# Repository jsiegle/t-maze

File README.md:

t-maze
======

Arduino-based hardware and software for controlling a maze

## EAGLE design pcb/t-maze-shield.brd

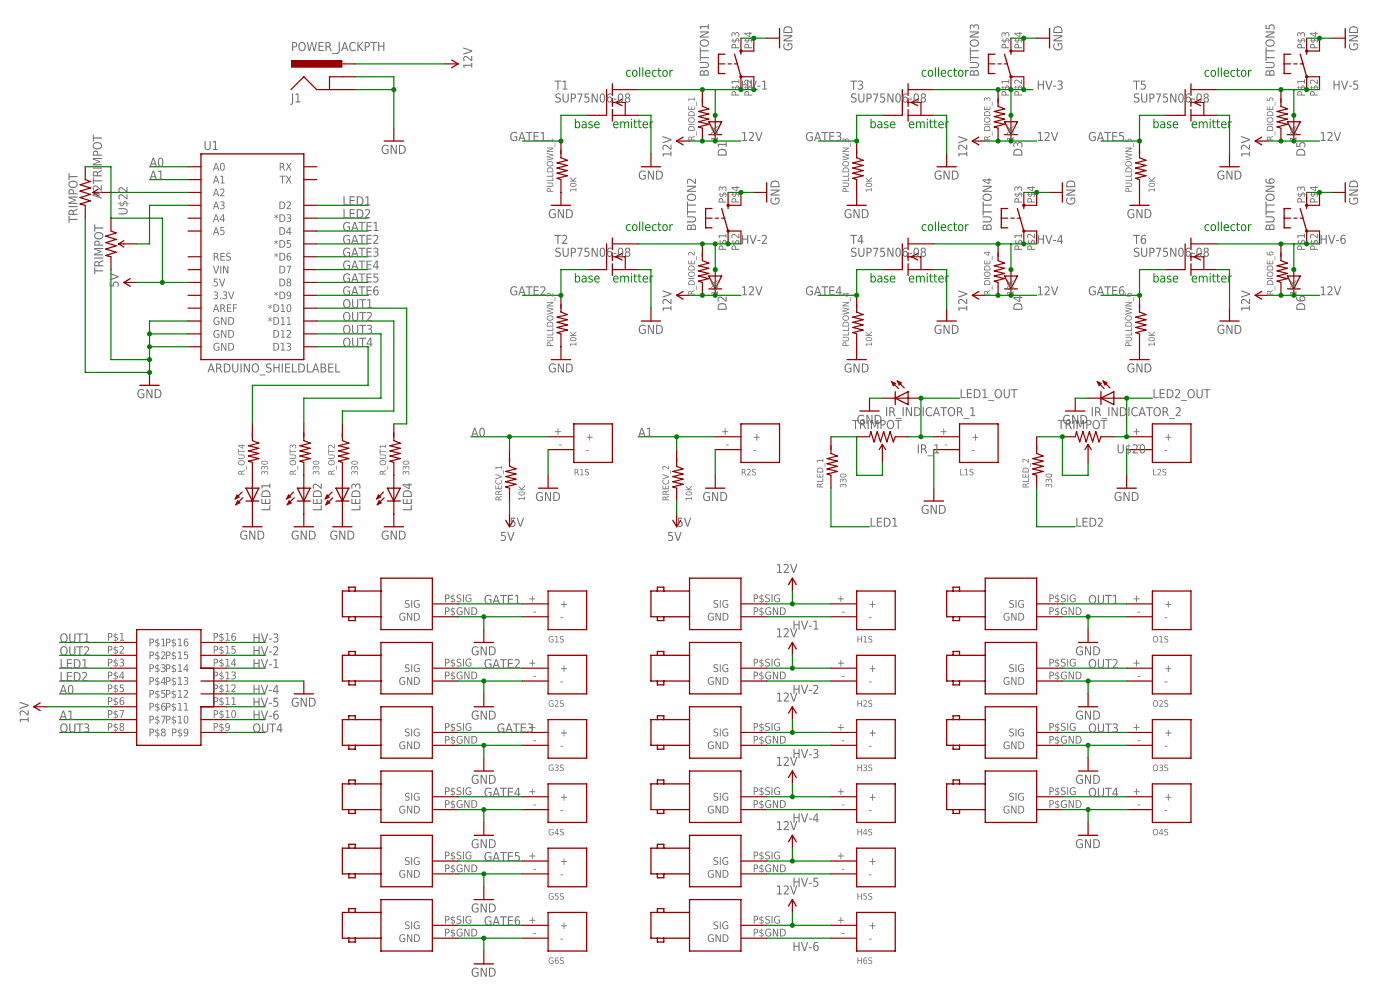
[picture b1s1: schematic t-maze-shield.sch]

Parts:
A2TRIMPOT: TRIMPOT; 3362U-2
BUTTON1, BUTTON2, BUTTON3, BUTTON4, BUTTON5, BUTTON6: TAC_SWITCHKSA_SEALED; KSA_SEALED_TAC_SWITCH
D1, D2, D3, D4, D5, D6: DIODE1N4148; DIODE-1N4148
G1S, G2S, G3S, G4S, G5S, G6S: SCREW_TERM_2; SCREW_TERM
GATE1, GATE2, GATE3, GATE4, GATE5, GATE6: BNC_RIGHT_ANGLE
H1S, H2S, H3S, H4S, H5S, H6S: SCREW_TERM_2; SCREW_TERM
I/O1, I/O2, I/O3, I/O4: BNC_RIGHT_ANGLE
IDC-16: IDC_16PIN
IR_1: TRIMPOT; 3362U-2
IR_INDICATOR_1, IR_INDICATOR_2: LED5MM
J1: POWER_JACKPTH; POWER_JACK_PTH
L1S, L2S: SCREW_TERM_2; SCREW_TERM
LED1, LED2, LED3, LED4: LED5MM
O1S, O2S, O3S, O4S: SCREW_TERM_2; SCREW_TERM
OUT1, OUT2, OUT3, OUT4, OUT5, OUT6: BNC_RIGHT_ANGLE
PULLDOWN_1, PULLDOWN_2, PULLDOWN_3, PULLDOWN_4, PULLDOWN_5, PULLDOWN_6: 10K; RESISTOR_PTH
R1S, R2S: SCREW_TERM_2; SCREW_TERM
RLED_1, RLED_2: 330; RESISTOR_PTH
RRECV_1, RRECV_2: 10K; RESISTOR_PTH
R_DIODE_1, R_DIODE_2, R_DIODE_3, R_DIODE_4, R_DIODE_5, R_DIODE_6: 10K; RESISTOR_PTH
R_OUT1, R_OUT2, R_OUT3, R_OUT4: 330; RESISTOR_PTH
T1, T2, T3, T4, T5, T6: SUP75N06-08; TO220
U1: ARDUINO_SHIELDLABEL; DUEMILANOVE_SHIELD
U$20, U$22: TRIMPOT; 3362U-2

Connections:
5V: A2TRIMPOT.1 (CCW), RRECV_1.P$1, RRECV_2.P$1, U1.5V, U$22.1 (CCW)
12V: D1.C, D2.C, D3.C, D4.C, D5.C, D6.C, H1S.+, H2S.+, H3S.+, H4S.+, H5S.+, H6S.+, IDC-16.P$6, J1.PWR, OUT1.P$SIG (SIG), OUT2.P$SIG (SIG), OUT3.P$SIG (SIG), OUT4.P$SIG (SIG), OUT5.P$SIG (SIG), OUT6.P$SIG (SIG), R_DIODE_1.P$1, R_DIODE_2.P$1, R_DIODE_3.P$1, R_DIODE_4.P$1, R_DIODE_5.P$1, R_DIODE_6.P$1
A0: IDC-16.P$5, R1S.+, RRECV_1.P$2, U1.A0
A1: IDC-16.P$7, R2S.+, RRECV_2.P$2, U1.A1
A3TRIMPOT: U1.A3, U$22.2 (WIPER)
GATE1: G1S.+, GATE1.P$SIG (SIG), PULLDOWN_1.P$2, T1.1 (G), U1.D4
GATE2: G2S.+, GATE2.P$SIG (SIG), PULLDOWN_2.P$2, T2.1 (G), U1.D5 (*D5)
GATE3: G3S.+, GATE3.P$SIG (SIG), PULLDOWN_3.P$2, T3.1 (G), U1.D6 (*D6)
GATE4: G4S.+, GATE4.P$SIG (SIG), PULLDOWN_4.P$2, T4.1 (G), U1.D7
GATE5: G5S.+, GATE5.P$SIG (SIG), PULLDOWN_5.P$2, T5.1 (G), U1.D8
GATE6: G6S.+, GATE6.P$SIG (SIG), PULLDOWN_6.P$2, T6.1 (G), U1.D9 (*D9)
GND: A2TRIMPOT.3 (CW), BUTTON1.P$3 (3), BUTTON1.P$4 (4), BUTTON2.P$3 (3), BUTTON2.P$4 (4), BUTTON3.P$3 (3), BUTTON3.P$4 (4), BUTTON4.P$3 (3), BUTTON4.P$4 (4), BUTTON5.P$3 (3), BUTTON5.P$4 (4), BUTTON6.P$3 (3), BUTTON6.P$4 (4), G1S.-, G2S.-, G3S.-, G4S.-, G5S.-, G6S.-, GATE1.P$GND (GND), GATE2.P$GND (GND), GATE3.P$GND (GND), GATE4.P$GND (GND), GATE5.P$GND (GND), GATE6.P$GND (GND), I/O1.P$GND (GND), I/O2.P$GND (GND), I/O3.P$GND (GND), I/O4.P$GND (GND), IDC-16.P$13, IR_INDICATOR_1.K (C), IR_INDICATOR_2.K (C), J1.GND, J1.GNDBREAK, L1S.-, L2S.-, LED1.K (C), LED2.K (C), LED3.K (C), LED4.K (C), O1S.-, O2S.-, O3S.-, O4S.-, PULLDOWN_1.P$1, PULLDOWN_2.P$1, PULLDOWN_3.P$1, PULLDOWN_4.P$1, PULLDOWN_5.P$1, PULLDOWN_6.P$1, R1S.-, R2S.-, T1.3 (S), T2.3 (S), T3.3 (S), T4.3 (S), T5.3 (S), T6.3 (S), U1.GND@0 (GND), U1.GND@1 (GND), U1.GND@2 (GND), U$22.3 (CW)
HV-1: BUTTON1.P$1 (1), BUTTON1.P$2 (2), D1.A, H1S.-, IDC-16.P$14, OUT1.P$GND (GND), R_DIODE_1.P$2, T1.2 (D)
HV-2: BUTTON2.P$1 (1), BUTTON2.P$2 (2), D2.A, H2S.-, IDC-16.P$15, OUT2.P$GND (GND), R_DIODE_2.P$2, T2.2 (D)
HV-3: BUTTON3.P$1 (1), BUTTON3.P$2 (2), D3.A, H3S.-, IDC-16.P$16, OUT3.P$GND (GND), R_DIODE_3.P$2, T3.2 (D)
HV-4: BUTTON4.P$1 (1), BUTTON4.P$2 (2), D4.A, H4S.-, IDC-16.P$12, OUT4.P$GND (GND), R_DIODE_4.P$2, T4.2 (D)
HV-5: BUTTON5.P$1 (1), BUTTON5.P$2 (2), D5.A, H5S.-, IDC-16.P$11, OUT5.P$GND (GND), R_DIODE_5.P$2, T5.2 (D)
HV-6: BUTTON6.P$1 (1), BUTTON6.P$2 (2), D6.A, H6S.-, IDC-16.P$10, OUT6.P$GND (GND), R_DIODE_6.P$2, T6.2 (D)
IR_2: RLED_2.P$2, U$20.2 (WIPER), U$20.3 (CW)
LED1: IDC-16.P$3, RLED_1.P$1, U1.D2
LED1_OUT: IR_1.1 (CCW), IR_INDICATOR_1.A, L1S.+
LED2: IDC-16.P$4, RLED_2.P$1, U1.D3 (*D3)
LED2_OUT: IR_INDICATOR_2.A, L2S.+, U$20.1 (CCW)
unnamed: LED4.A, R_OUT1.P$1
unnamed: LED3.A, R_OUT2.P$1
unnamed: IR_1.2 (WIPER), IR_1.3 (CW), RLED_1.P$2
unnamed: LED2.A, R_OUT3.P$1
unnamed: LED1.A, R_OUT4.P$1
unnamed: A2TRIMPOT.2 (WIPER), U1.A2
OUT1: I/O1.P$SIG (SIG), IDC-16.P$1, O1S.+, R_OUT1.P$2, U1.D10 (*D10)
OUT2: I/O2.P$SIG (SIG), IDC-16.P$2, O2S.+, R_OUT2.P$2, U1.D11 (*D11)
OUT3: I/O3.P$SIG (SIG), IDC-16.P$8, O3S.+, R_OUT3.P$2, U1.D12
OUT4: I/O4.P$SIG (SIG), IDC-16.P$9, O4S.+, R_OUT4.P$2, U1.D13

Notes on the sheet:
base
collector
emitter

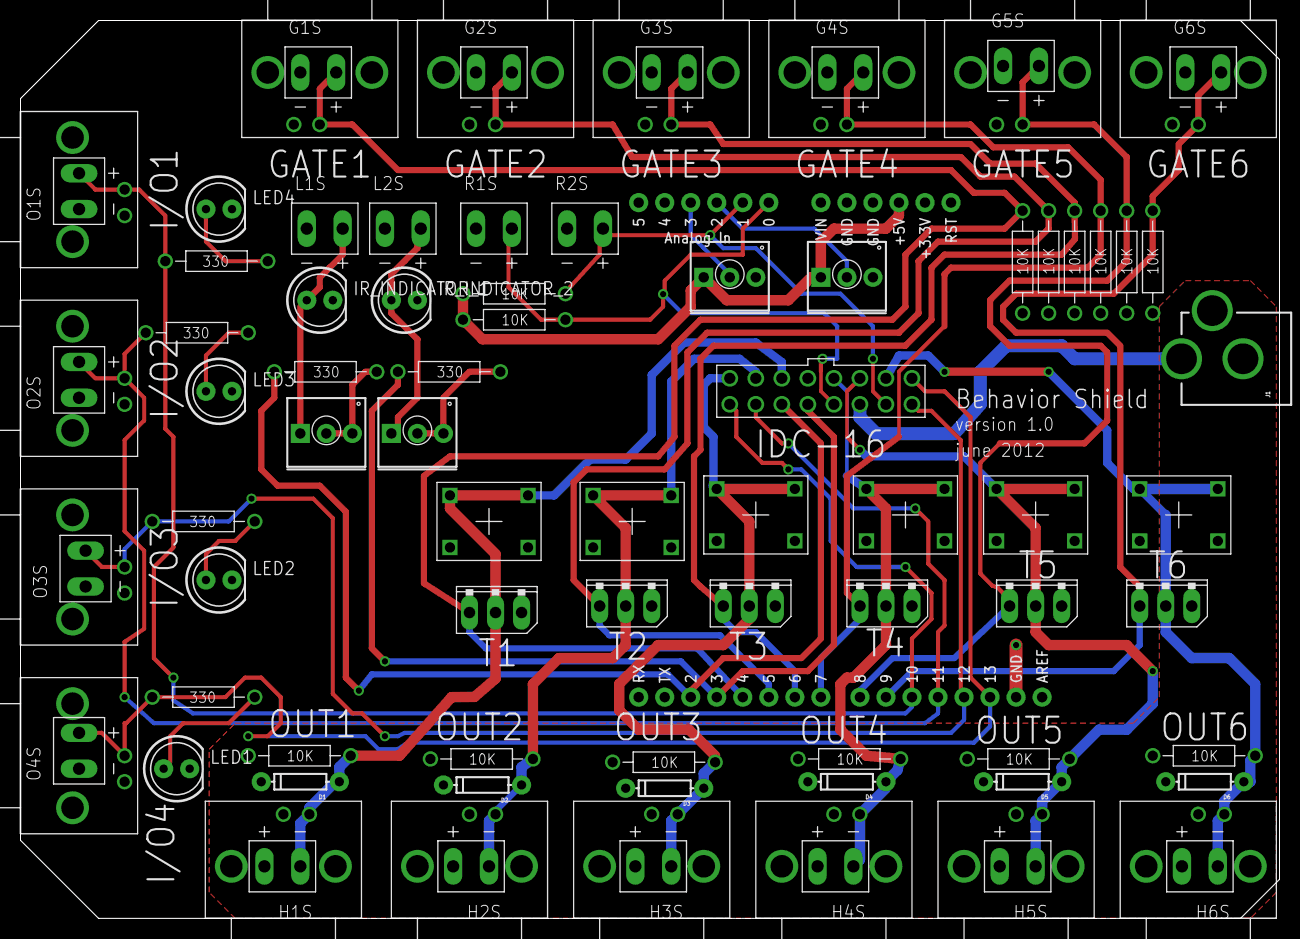
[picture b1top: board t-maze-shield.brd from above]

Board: 2 copper layers, 122.9 x 87.6 mm, 87 parts (0 on the bottom side), 33 nets.

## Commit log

2014-07-07 Add .gitignore file
2014-07-07 Initial commit of files
2014-11-13 Add Arduino code
